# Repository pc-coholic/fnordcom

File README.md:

fnordcom
========

ClearCom-compatible beltpacks for the masses

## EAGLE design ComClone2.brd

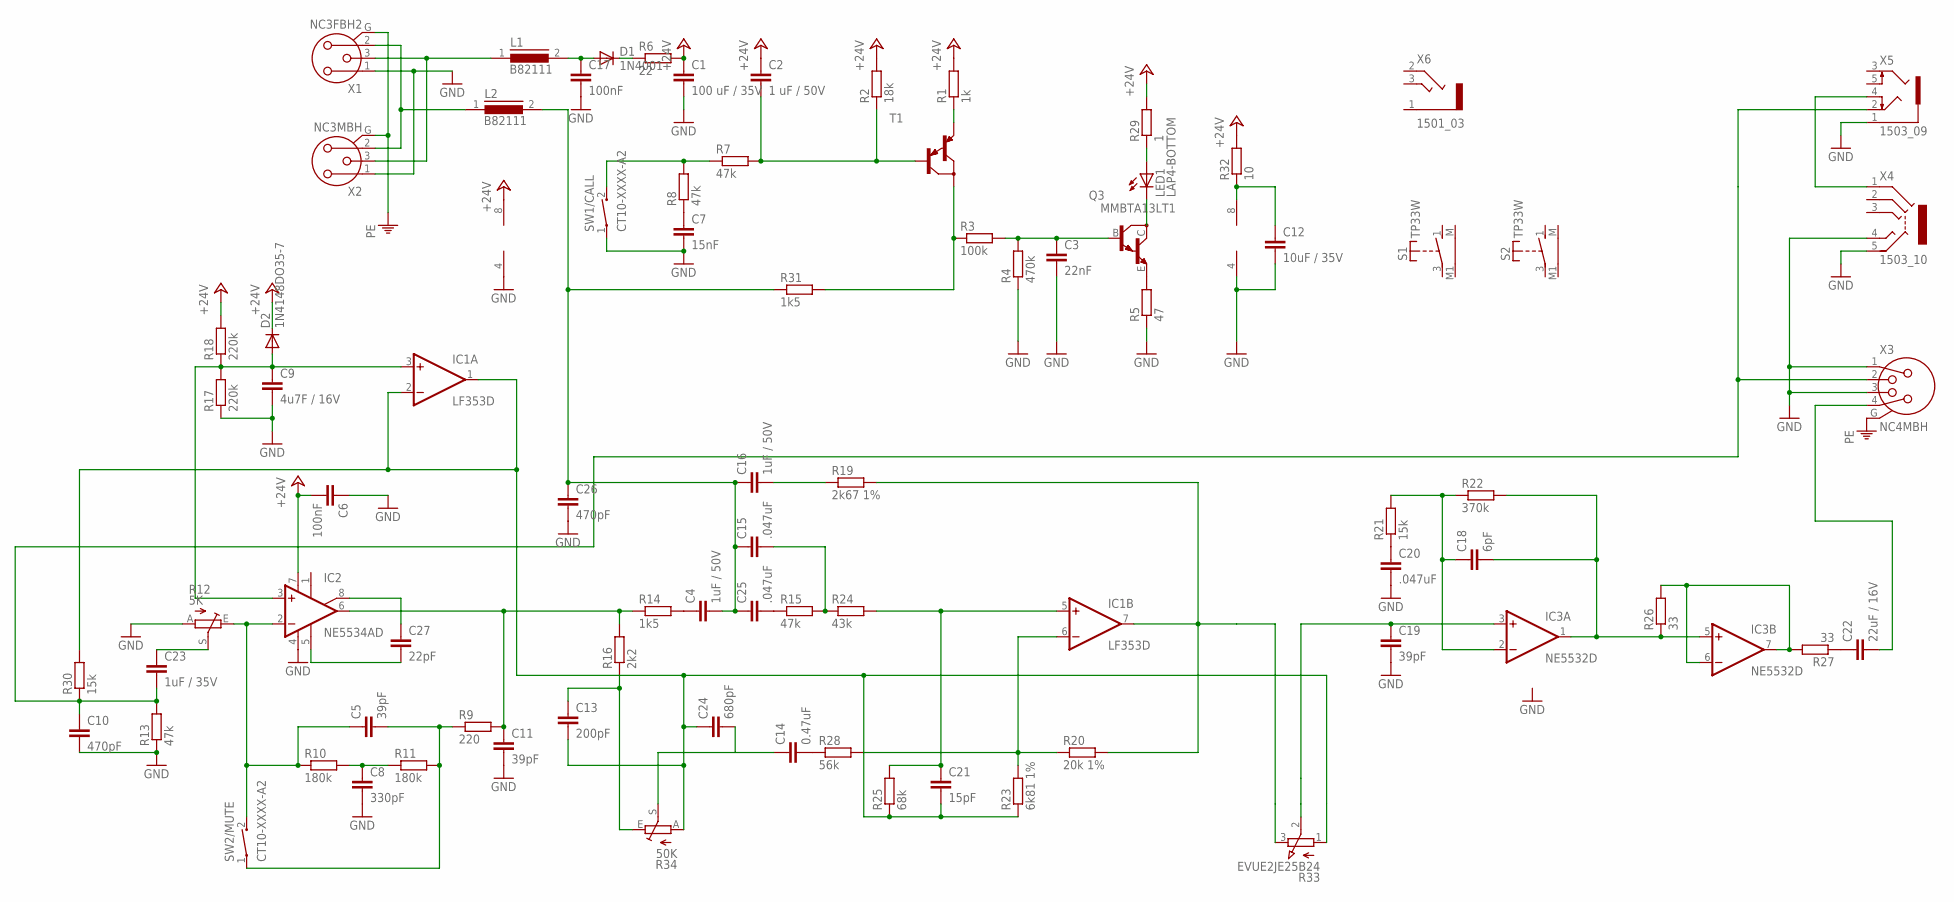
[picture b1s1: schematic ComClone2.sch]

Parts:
C1: 100 uF / 35V; C1206
C2: 1 uF / 50V; C1206
C3: 22nF; C0603
C4: 1uF / 50V; C1206
C5, C11: 39pF; C0603
C6, C17: 100nF; C1206
C7: 15nF; C0603
C8: 330pF; C0603
C9: 4u7F / 16V; C1206
C10, C26: 470pF; C0603
C12: 10uF / 35V; C1206
C13: 200pF; C0603
C14: 0.47uF; C0603
C15, C20: .047uF; C1206
C16: 1uF / 50V; C3225
C18: 6pF; C1206
C19: 39pF; C1206
C21: 15pF; C1206
C22: 22uF / 16V; C1206
C23: 1uF / 35V; C1206
C24: 680pF; C0603
C25: .047uF; C0603
C27: 22pF; C0603
D1: 1N4001; DO41-10
D2: 1N4148DO35-7; DO35-7
IC1: LF353D; SO08
IC2: NE5534AD; SO08
IC3: NE5532D; SO08
L1, L2: B82111; SUKW1-30
LED1: LAP4-BOTTOM; P47F-BOTTOM
Q3: MMBTA13LT1; SOT23-BEC
R1: 1k; R0603
R2: 18k; R0603
R3: 100k; R0603
R4: 470k; R0603
R5: 47; M1206
R6: 22; M1206
R7, R8, R13, R15: 47k; R0603
R9: 220; R0603
R10, R11: 180k; R0603
R12: 5K; PT-10S
R14, R31: 1k5; R0603
R16: 2k2; R0603
R17, R18: 220k; M1206
R19: 2k67 1%; M1206
R20: 20k 1%; R0603
R21: 15k; M1206
R22: 370k; R0603
R23: 6k81 1%; R0603
R24: 43k; R0603
R25: 68k; R0603
R26, R27: 33; M1206
R28: 56k; R0603
R29: 1; M1206
R30: 15k; R0603
R32: 10; M1206
R33: EVUE2JE25B24; EVUEXXJ
R34: 50K; PT-10S
S1, S2: TP33W
SW1/CALL, SW2/MUTE: CT10-XXXX-A2
T1: MMBTA64LT1-PNP_DARL-SOT23-BEC; SOT23-BEC
X1: NC3FBH2
X2: NC3MBH
X3: NC4MBH
X4: 1503_10
X5: 1503_09
X6: 1501_03

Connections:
+24V: C1.1, C2.1, C6.2, D2.C, IC1.8 (V+), IC2.7 (V+), R1.2, R2.2, R6.2, R18.2, R29.2, R32.2
GND: C1.2, C3.2, C6.1, C7.2, C8.2, C9.2, C10.2, C11.2, C12.2, C17.2, C19.2, C20.2, C26.2, IC1.4 (V-), IC2.4 (V-), IC3.4 (V-), R4.1, R5.1, R12.A, R13.1, R17.1, SW1/CALL.1, X1.1, X2.1, X3.1, X3.3, X4.4, X4.5, X5.1
unnamed: L1.1, X1.3, X2.3
unnamed: C3.1, Q3.B, R3.2, R4.2
unnamed: C12.1, IC3.8 (V+), R32.1
unnamed: C27.1, IC2.8 (ON/CMP)
unnamed: D1.C, R6.1
unnamed: C5.1, IC2.2 (-IN), R10.1, R12.E, SW2/MUTE.2
unnamed: C2.2, R2.1, R7.2, T1.B
unnamed: C7.1, R8.1
unnamed: R7.1, R8.2, SW1/CALL.2
unnamed: R1.1, T1.E
unnamed: R3.1, R31.2, T1.C
unnamed: IC3.6 (-IN), IC3.7 (OUT), R26.2, R27.2
unnamed: Q3.E, R5.2
unnamed: LED1.C, Q3.C
unnamed: LED1.A, R29.1
unnamed: C9.1, D2.A, IC1.3 (+IN), IC2.3 (+IN), R17.2, R18.1
unnamed: C14.1, C24.2, R34.S
unnamed: C23.1, R12.S
unnamed: C10.1, C23.2, R13.2, R30.1, X3.2, X5.2
unnamed: C11.1, IC2.6 (OUT), R9.2, R14.1, R16.2
unnamed: C13.2, C21.2, C24.1, IC1.1 (OUT), IC1.2 (-IN), R23.1, R25.1, R30.2, R33.1 (A), R34.A
unnamed: C8.1, R10.2, R11.1
unnamed: C4.1, R14.2
unnamed: C5.2, R9.1, R11.2, SW2/MUTE.1
unnamed: C13.1, R16.1, R34.E
unnamed: C14.2, R28.1
unnamed: C17.1, D1.A, L1.2
unnamed: C25.2, R15.1
unnamed: C15.2, R15.2, R24.1
unnamed: C16.2, R19.1
unnamed: C21.1, IC1.5 (+IN), R24.2, R25.2
unnamed: IC1.7 (OUT), R19.2, R20.2, R33.3 (E)
unnamed: IC1.6 (-IN), R20.1, R23.2, R28.2
unnamed: C22.1, R27.1
unnamed: C19.1, IC3.3 (+IN), R33.2 (S)
unnamed: C18.1, IC3.2 (-IN), R21.2, R22.1
unnamed: C18.2, IC3.1 (OUT), IC3.5 (+IN), R22.2, R26.1
unnamed: C20.1, R21.1
unnamed: L2.1, X1.2, X2.2
unnamed: C22.2, X3.4
unnamed: X4.1, X5.4
unnamed: C4.2, C15.1, C16.1, C25.1, C26.1, L2.2, R31.1
unnamed: C27.2, IC2.5 (CMP)
PE: X1.G, X2.G, X3.G

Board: 2 copper layers, 81 parts (0 on the bottom side), 46 nets, no tracks yet.

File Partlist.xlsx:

|  | Reichelt | RS | Farnell | Mouser
R1 | 1K | SMD-0603 1K |  |  |  | 0.1
R2 | 18K | SMD-0603 18K |  |  |  | 0.1
R3 | 100K | SMD-0603 100K |  |  |  | 0.1
R4 | 470K | SMD-0603 470K |  |  |  | 0.1
R5 | 47R | SMD 1/4W 47 |  |  |  | 0.1
R6 | 22R | SMD 1/4W 22 |  |  |  | 0.1
R7 | 47K | SMD-0603 47K |  |  |  | 0.1
R8 | 47K | SMD-0603 47K |  |  |  | 0.1
R9 | 220R | SMD-0603 220 |  |  |  | 0.08
R10 | 180K | SMD-0603 180K |  |  |  | 0.1
R11 | 180K | SMD-0603 180K |  |  |  | 0.1
R12 | 10K Trim | PT 10-S 5,0K |  |  |  | 0.22
R13 | 47K | SMD-0603 47K |  |  |  | 0.1
R14 | 1K5 | SMD-0603 1,5K |  |  |  | 0.1
R15 | 47K | SMD-0603 47K |  |  |  | 0.1
R16 | 2K2 | SMD-0603 2,2K |  |  |  | 0.1
R17 | 220K | SMD-0603 220K |  |  |  | 0.08
R18 | 220K | SMD-0603 220K |  |  |  | 0.1
R19 | 2K67 |  |  |  |  | 0.1
R20 | 20K |  |  |  |  | 0.1
R21 | 15K | SMD-0603 15K |  |  |  | 0.1
R22 | 370K |  |  |  |  | 0.1
R23 | 6K8 | SMD-0603 6K8 |  |  |  | 0.1
R24 | 43K |  |  |  |  | 0.1
R25 | 68K | SMD-0603 68K |  |  |  | 0.1
R26 | 33R | SMD 1/4W 33 |  |  |  | 0.1
R27 | 33R | SMD 1/4W 33 |  |  |  | 0.1
R28 | 56K | SMD-0603 56K |  |  |  | 0.1
R29 | Lampen-R
R30
R31 | 1K5 | SMD-0603 1,5K |  |  |  | 0.1
R32 | 10R | SMD 1/4W 10 |  |  |  | 0.1
R33 | 20K EVUE2JFK4B24 | (RK11K112-LOG10K) |  |  | 667-EVU-E2JFK4B24 | 0.5
R34 | 50 K Trim | PT 10-S 50K |  |  |  | 0.22
C1 | 100uF 35V | RAD FC 100/50 |  |  |  | 0.21
C2 | 1uF | X7R-G1206 1,0/50 |  |  |  | 0.04
C3 | 22nF | X7R-G0603 22N |  |  |  | 0.05
C4 | 1uF | SMD-2824N 1,0u |  |  |  | 0.63
C5 | 39pF |  |  |  |  | 0.1
C6 | 100nF | X7R-G0603 100N |  |  |  | 0.05
C7 | 15nF |  |  |  |  | 0.1
C8 | 330pF | NP0-G0603 220P |  |  |  | 0.05
C9 | 4u7 | RAD FC 4,7/50 |  |  |  | 0.09
C10 | 470pF |  |  |  |  | 0.1
C11 | 39pF |  |  |  |  | 0.1
C12 | 10uF |  |  |  |  | 0.1
C13 | 200pF |  |  |  |  | 0.1
C14 | 47nF |  |  |  |  | 0.1
C15 | 47nF |  |  |  |  | 0.1
C16 | 1uF | SMD-2824N 1,0u |  |  |  | 0.63
C17 | 100nF | X7R-G0603 100N |  |  |  | 0.05
C18 | 6pF |  |  |  |  | 0.1
C19 | 39pF |  |  |  |  | 0.1
C20 | 47nF |  |  |  |  | 0.1
C21 | 15pF |  |  |  |  | 0.1
C22 | 22uF | RAD FC 22/50 |  |  |  | 0.09
C23 | 1uF | SMD-2824N 1,0u |  |  |  | 0.63
C24 | 680pF |  |  |  |  | 0.1
C25 | 47nF |  |  |  |  | 0.1
C26 | 470pF |  |  |  |  | 0.1
C27 | 22pF | NP0-G0603 22P |  |  |  | 0.05
L1 | 330uH | 77A 330u |  |  |  | 0.73
L2 | 330uH | 77A 330u |  |  |  | 0.73
D1 | 1N4007 | 1N 4007 SMD |  |  |  | 0.05
D2 | 1N418 | 1N 4148 SMD |  |  |  | 0.02
D3/D4 | Mentor 1801.8231 | MEN 1801.8231 |  |  |  | 0.91
Q1 | MMBTA63 | (BCV 47 SMD) |  |  | 512-MMBTA63 | 0.19
Q2 | MMBTA13 | (BCV 27 SMD) |  |  | 512-MMBTA13 | 0.19
U1 | NE5534D | NE 5534 D SMD |  |  |  | 0.34
U2 | LF353 | LF 353 M |  |  |  | 0.63
U3 | NE5532D | NE 5532 D8 SMD |  |  |  | 0.26
S1 | Apem TP33WW080 |  | 664-389 | 1082510 |  | 3.94
S2 | Apem TP33WW080 |  | 664-389 | 1082510 |  | 3.94
(S1) | Apem U576 Kappe rot |  | 664-430 |  |  | 0.36
(S2) | Apem U573Kappe Grün |  | 664-424 |  |  | 0.28999999999999998
X1 | Neutrix NC3FBH2 |  |  |  | 568-NC3FBH-2 | 2.42
X2 | Neutrix NC3MBH |  |  |  | 568-NC3MBH | 2.42
X3 | Neutrix NC4MBH |  |  |  | 568-NC4MBH | 3.7
X4 | Lumberg 1503-10 |  |  | 1308868 |  | 2.72
X5 | Lumberg 1503-6 |  |  | 1243243 |  | 2.48
X6 | Lumberg 1503 03 |  |  | 1200127 |  | 1.36
 |  |  |  |  |  | 35.54999999999999

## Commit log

2013-10-13 Initial import
